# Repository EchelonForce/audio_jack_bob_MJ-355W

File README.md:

# Audio Jack Breakout Board MJ-355W

This is a PCB for a breakout board for use while breadboarding with the MJ-355W audio jack or the Thonkiconn audio jack.

Full writeup here: https://www.robotdialogs.com/2022/08/breakout-boards-for-synthesizer.html

This work is licensed under a Creative Commons Attribution-NonCommercial-ShareAlike 4.0 International License. https://creativecommons.org/licenses/by-nc-sa/4.0/

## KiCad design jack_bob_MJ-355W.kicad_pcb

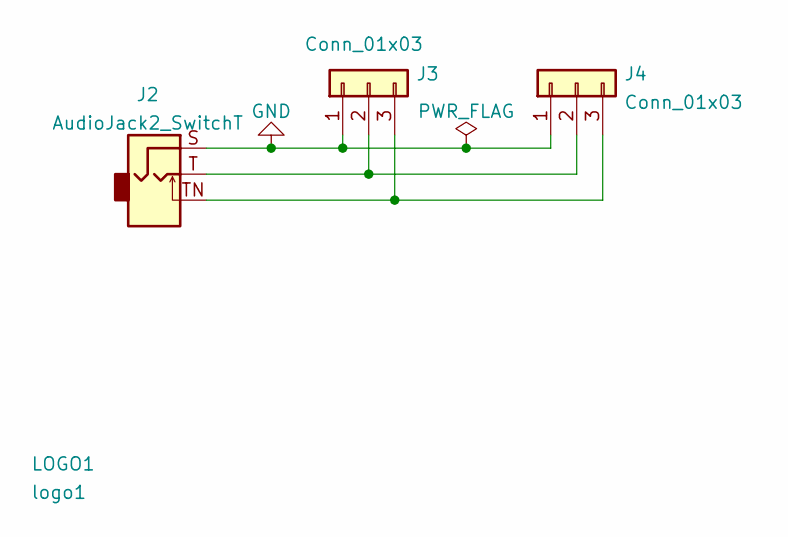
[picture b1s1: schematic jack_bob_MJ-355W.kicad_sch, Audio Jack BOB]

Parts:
J2: AudioJack2_SwitchT; Jack_3.5mm_MJ-355W_and_PJ398SM_Vertical
J3, J4: Conn_01x03; PinHeader_1x03_P2.54mm_Vertical
LOGO1: logo1; Logo1

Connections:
GND: J2.S, J3.1, J4.1
unnamed: J2.T, J3.2, J4.2
unnamed: J2.TN, J3.3, J4.3

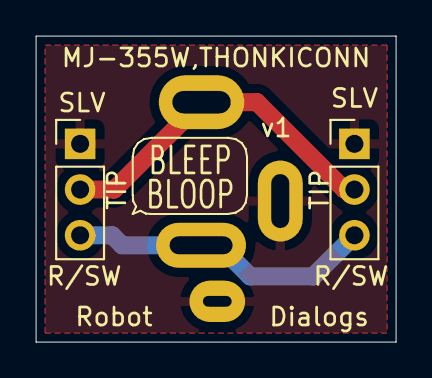
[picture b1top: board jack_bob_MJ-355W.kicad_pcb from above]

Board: 2 copper layers, 20.0 x 17.0 mm, 4 parts (1 on the bottom side), 3 nets.

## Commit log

2022-02-19 Initial commit with .gitignore
2022-02-19 Version 1 PCB as ordered
2022-08-31 Add readme
